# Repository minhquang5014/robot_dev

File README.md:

# robot_dev — Trợ lý giọng nói xiaozhi trên ESP32

Môi trường làm việc cho ESP32 + mic I2S + khuếch đại I2S, chạy firmware
[xiaozhi-esp32](https://github.com/78/xiaozhi-esp32) (MIT) đã tuỳ chỉnh.

## Phần cứng

| Linh kiện | Chi tiết |
|---|---|
| MCU | ESP32-S3-WROOM-1 **N16R8** — 16MB flash, 8MB PSRAM (octal) |
| Mic | INMP441 (I2S) |
| Khuếch đại | MAX98357A (I2S) + loa 4–8Ω |
| Màn hình | OLED SSD1306 128x64 (I2C) |
| Chân robot | 4 servo SG90/MG90S (2 hông + 2 cổ chân) |

Trước 11/10/2026 dự án chạy ESP32-D0WD-V3 4MB **không có PSRAM**. Đổi sang S3 vì
hai lý do: con cũ chết chip USB-serial (cắm 5 lần không lên cổng COM nào), và
PSRAM là điều kiện bắt buộc để chạy wake word trên chip. Board cũ vẫn còn trong
repo ở `main/boards/bread-compact-esp32/`.

### Sơ đồ đấu nối

```
INMP441         ESP32-S3        MAX98357A       ESP32-S3
  VDD    ->      3V3              VIN     ->      5V
  GND    ->      GND              GND     ->      GND
  L/R    ->      GND              DIN     ->      GPIO7
  WS     ->      GPIO4            BCLK    ->      GPIO15
  SCK    ->      GPIO5            LRC     ->      GPIO16
  SD     ->      GPIO6            GAIN    ->      GND (12dB)
                                  SD      ->      để trống
OLED SSD1306    ESP32-S3          +/-     ->      loa 4-8Ω
  VCC    ->      3V3
  GND    ->      GND          Nút BOOT (GPIO0, có sẵn) = bắt đầu/dừng hội thoại
  SDA    ->      GPIO41       GPIO38 = giả lập câu đánh thức
  SCL    ->      GPIO42       GPIO47 = bộ đàm, giữ để nói

Hông trái	GPIO13
Hông phải	GPIO14
Cổ chân trái	GPIO21
Cổ chân phải	GPIO12
```

Tất cả GND chung.

Bản vẽ minh hoạ: [ESP32-S3 Robot Wiring Diagram.png](ESP32-S3%20Robot%20Wiring%20Diagram.png).
Đường dây từ linh kiện tới chân S3 trong ảnh khớp sơ đồ trên, nhưng **lấy sơ đồ chữ
ở trên làm chuẩn** vì ảnh có lỗi:

- Ô "Lưu ý khi hàn dây" ghi servo dùng 3.3V — **sai**, servo dùng 5V nguồn riêng (xem dưới).
- Bảng "Tóm tắt kết nối" lỗi chữ: mic `WS → GPIO45` (đúng là **GPIO4**), `GPIO0 → 3V3`;
  amp `DIN → 5V7`, `LRC → GPIO` thiếu số (đúng: DIN GPIO7, LRC GPIO16).
- Ảnh mic là module electret, không phải INMP441. Servo chỉ vẽ dây tín hiệu, thiếu dây nguồn.
- Nút GPIO38 / GPIO47 chỉ vẽ một dây — chân còn lại của nút nối **GND**.

**Servo phải có nguồn 5V riêng**, chỉ chung mát với board. Lấy từ chân 5V của
DevKitC-1 thì lúc servo giật sẽ kéo sụt cả đường nguồn của S3. Và `MAX98357A VIN`
nối thẳng VBUS không qua ổn áp nào — nên cắm USB qua hub hay cáp kém là tiếng loa
nhỏ hẳn đi. Hàn tụ ~1000 µF sát chân VIN của amp.

**Chân không dùng được trên S3**, khác hẳn ESP32 cũ nên đừng chép sơ đồ cũ sang:

| Chân | Lý do |
|---|---|
| GPIO22–25 | không tồn tại trên S3 (nhảy từ 21 sang 26) |
| GPIO26–32 | SPI flash |
| GPIO33–37 | PSRAM octal của bản R8 |
| GPIO19, 20 | USB D−/D+ |
| GPIO0, 3, 45, 46 | strapping |
| GPIO43, 44 | UART0 (console) |

GPIO12 là chân strapping trên **ESP32 cũ** nhưng **không phải** trên S3, nên ở đây
dùng được cho servo.

### Nguồn pin

| Linh kiện | Chi tiết |
|---|---|
| Pin | LiPo 1 cell **3,7V 3000 mAh**, có mạch bảo vệ (PCM) — mảnh mạch nhỏ dưới băng dính vàng ở đầu pin |
| Sạc + tăng áp | Module Type-C **FM5324GA** (25 x 20 mm): sạc pin qua Type-C, tăng 3,7V lên 5V |
| Công tắc | **Từ 3A trở lên** (ví dụ bập bênh KCD1). Gạt mini SS12D00 / MSK12C02 chỉ 0,3-0,5A — nóng, sụt áp |

```
Pin (+) đỏ ──[CÔNG TẮC ≥3A]── B+ ┐
Pin (−) đen ──────────────────── B− ┤  FM5324GA   5V  ──┬─► ESP32-S3 chân 5V
                                    │             GND ──┼─► GND chung (mọi thứ)
             nút nhấn nhả ── K ─────┘  [Type-C] = sạc   ├─► MAX98357A VIN  (+ tụ 1000 µF)
             (chân kia xuống GND)                       └─► 4 servo dây đỏ (+ tụ 1000 µF)
```

**Chưa chắc chân nào là B+ / B−.** Nhìn ảnh module thì hai miếng hàn cạnh TRÁI (ký hiệu
"□" và "+") là pin, cạnh DƯỚI ("+" và "5V") là ngõ ra — nhưng phải đo trước khi hàn,
ngược cực pin là cháy: cắm Type-C (chưa nối pin), miếng ra ~4,2V là B+, miếng ra ~5V là
ngõ ra; B− thông mạch với GND của ngõ ra.

**Công tắc đặt trên dây đỏ của pin** chứ không phải ở ngõ ra 5V: khi bật tăng áp, module
ăn điện liên tục, ngắt ở ngõ ra thì robot tắt nhưng pin vẫn bị rút. Cái giá: **tắt công
tắc thì không sạc được** — nhớ bật lên khi cắm sạc.

#### Chân K (bật / tắt ngõ ra 5V) — đo ngày 16/10/2026

| Thử | Kết quả |
|---|---|
| Cắm pin, chưa làm gì | Ngõ ra ~3,8V = điện áp pin lọt qua cuộn cảm + diode, **tăng áp chưa chạy** |
| Chạm K xuống GND một cái | Lên **5V** |
| **Hàn cứng K xuống GND** | Giữ 5V được vài phút rồi **tụt xuống 1,6V** — chip hiểu K bị giữ mãi là "nhấn giữ = tắt", tụ ngõ ra xả dần qua đồng hồ đo |

→ **Không hàn cứng K xuống GND.** Dùng K làm nút nguồn (nút nhấn nhả, giống sạc dự phòng):
nhấn một cái để bật. Lúc thử trên chỉ có đồng hồ đo làm tải (gần như 0 mA) — có robot
làm tải (ESP32-S3 ~100 mA trở lên) thì nhiều khả năng mạch không tự tắt. **CHƯA kiểm
chứng:** cắm robot, nhấn K, để chạy 15 phút xem có tự tắt không.

#### Nếu có robot làm tải mà vẫn tự tắt — ESP32 giữ cho mạch thức (CHƯA làm)

Đừng để ESP32 *chờ thấy điện yếu rồi mới* kéo K: ESP32 lấy điện từ chính module này, lúc
tăng áp tắt thì ngõ ra tụt về ≤3,8V, ổn áp 3,3V trên board không đủ đầu vào nên chip sụt áp
và reset trước khi kịp phản ứng. Thay vào đó **nhấn K ngắn theo nhịp, mỗi ~15-20 giây**, để
mạch không bao giờ tự tắt.

Phải thử trước: chạm K xuống GND **thật nhanh (dưới nửa giây) trong lúc đang có 5V** — nếu
5V vẫn giữ thì cách này dùng được; nếu chip hiểu là bật/tắt thì không dùng được.

**Nối THẲNG, không cần transistor.** Chân K lúc nghỉ đo được **0,8V** (17/10/2026) — thấp hơn
3,3V nên nối thẳng vào GPIO không hại gì ESP32:

```
ESP32-S3 GPIO2 ─────── chân K của FM5324GA
```

- Đặt GPIO2 ở chế độ **open-drain**: chỉ có hai trạng thái — kéo xuống GND hoặc thả nổi,
  không bao giờ ra 3,3V. Kéo **xuống 0** ~200 ms rồi thả = một lần "nhấn nút".
- **Đừng** cho GPIO2 ra mức cao: đẩy 3,3V vào K (bình thường 0,8V) là cãi nhau với mạch
  trong chip sạc.
- Lúc ESP32 khởi động GPIO2 mặc định thả nổi nên không bị "nhấn nhầm".
- GPIO2 đang trống trên board S3 (soát với `bread-compact-s3-otto/config.h`).

**Dây K là BẮT BUỘC** — đo ngày 26/10/2026 trên ESP32 WROOM chạy pin, sketch
`test/fm_keepalive` (tự ghi log vào flash):

| Thử | Kết quả |
|---|---|
| ESP32 nhấn K mỗi 15 s (200 ms) | giữ 5V **33,2 phút liền**, 132 lần nhấn, 4,93-5,08V (TB 5,04V), không mất điện lần nào |
| Không nhấn K, ESP32 làm tải (WiFi quét định kỳ, ~100 mA) | mạch **tự tắt**, ngõ ra tụt ~1,5V, ESP32 tắt theo |

→ Nhấn ngắn khi đang bật **không** làm tắt (chip không hiểu là bật/tắt), và có tải vẫn tự tắt —
nên firmware robot phải nhấn K theo nhịp. Board ESP32 cũ (WROOM) dùng GPIO18 vì không ra chân
TX2/RX2; trên board cũ GPIO18 trùng `LAMP_GPIO`, lắp vào robot thì phải dời một trong hai.

**Cắm USB lúc đang chạy pin làm board reset liên tục** (log đầy `POWERON_RESET`) — hai nguồn 5V
đè nhau. Rút pin trước khi cắm USB.

**Đo điện áp pin — tuỳ chọn, có thể bỏ.** Chỉ để báo pin yếu lên OLED; không có thì robot vẫn
chạy, hết pin thì tắt phụt (mạch bảo vệ của pin ngắt ~3,0V, vẫn an toàn). 4 đèn LED trên
module báo mức pin thay được. Nếu muốn làm:

```
5V ──[10 kΩ]──┬──[10 kΩ]── GND
              └── ESP32-S3 GPIO1 (ADC)
```

Chân ADC của ESP32 chỉ đọc tới ~3V, nối thẳng 5V là hỏng. Hai điện trở bằng nhau chia đôi:
5V đọc ra 2,5V, trong code nhân 2. Đọc ~1,9V (tức 3,8V) = tăng áp đã tắt. Rút ~0,25 mA
liên tục; thêm tụ 100 nF từ điểm giữa xuống GND cho số đọc ổn định.

#### Đèn LED khi sạc

Cắm sạc thấy sáng 3/4 đèn dù pin đang ~3,0V là bình thường: lúc có dòng sạc, điện áp ở cực
pin bị đẩy cao hơn mức thật nên đèn báo dư. Muốn biết thật thì rút sạc, để nghỉ 10-15 phút
rồi đo ở hai dây pin (đầy ~4,1-4,2V).

Sạc bằng cục sạc MacBook (USB-C PD) an toàn: không xin thì PD chỉ cấp 5V. Nếu cáp C-to-C
cắm vào không sạc là module thiếu điện trở 5,1 kΩ ở chân CC — dùng cáp USB-A sang C với cục
sạc thường.

#### Pin 3000 mAh có đủ dòng không

Robot kéo tới ~2A ở 5V khi 4 servo cùng giật. Tăng áp lên 5V nên phía pin chịu dòng gấp
~1,6 lần: **pin phải xả ~3,2A**. Pin 3000 mAh dù chỉ xả 1C cũng đã ~3A, nên nhiều khả năng
đủ — nhưng **mạch bảo vệ (PCM) có ngưỡng ngắt quá dòng riêng**, có loại ngắt ở ~3A. Chưa
biết chỉ số xả (C) và ngưỡng PCM của pin này. Thử: cho robot nhảy cả bài trong lúc đang nói;
tắt hoặc reset giữa chừng là PCM đang ngắt.

Ước tính thời gian chạy (chưa đo): 3000 mAh x 3,7V ≈ 11 Wh, qua tăng áp còn ~9 Wh ở 5V →
đứng nghe (~150 mA) **khoảng 10-12 giờ**, nói và đi nhiều **khoảng 3 giờ**.

**Cắm USB nạp code khi đang chạy pin:** hai nguồn 5V có thể đè nhau. Tắt công tắc pin
trước khi cắm USB, hoặc nạp qua WiFi (OTA).

## Tuỳ chỉnh so với xiaozhi gốc

1. **Kết nối được WiFi ẩn** — `xiaozhi-esp32/components/esp-wifi-connect/wifi_station.cc`

   Bản gốc quét WiFi rồi so khớp theo tên. Mạng ẩn không phát tên trong beacon nên
   không bao giờ khớp, thiết bị kẹt ở `No AP found` vĩnh viễn. Bản vá thêm một
   nhánh dự phòng: khi quét không ra, thử kết nối thẳng từng mạng đã lưu —
   `esp_wifi_connect()` gửi probe request có đích danh, và mạng ẩn **có** trả lời.

   Đặt trong `components/` (không sửa `managed_components/`) để không bị ghi đè
   mỗi lần trình quản lý tải lại dependency.

2. **Giao diện tiếng Việt** — `CONFIG_LANGUAGE_VI_VN=y` trong `sdkconfig`.
   Cả chữ trên màn lẫn giọng đọc. Font mặc định đã phủ đủ 39 ký tự có dấu được dùng.

3. **OLED 128x64** — `CONFIG_OLED_SSD1306_128X64=y` (mặc định của board là 128x32).

4. **Đánh thức bằng tên "Sophia"** — `CONFIG_SR_WN_WN9_SOPHIA_TTS=y`.

   Thay cho `CONFIG_ALWAYS_LISTENING` cũ (rảnh ~5 giây là tự mở hội thoại). Chế độ
   cũ làm robot trả lời **mọi** câu nó nghe được và gửi tiếng lên server 100% thời
   gian; giờ nằm im cho tới khi nghe đúng tên.

   Vì sao là "Sophia": model WakeNet đóng gói sẵn trong `esp-sr` có 75 cái, lọc bỏ
   tiếng Trung còn 39 — **không có tiếng Việt**. Trong nhóm tên nữ, "Sophia" là cái
   **duy nhất gọi trống được**; mọi tên khác đều buộc kèm "Hey"/"Hi" (Hey Ivy,
   Hi Fairy…). Muốn đúng tên tiếng Việt thì phải đặt model riêng của Espressif.

   Ba thứ phải khớp nhau nếu đổi tên: model trong `sdkconfig`, chuỗi
   `WakeWordInvoke` trong board `.cc`, và `ROBOT_NAME`/`WAKE_PATTERN` trong
   `server/pipeline.py`.

   **Luồng:** nằm chờ ở Idle, không gửi gì lên mạng — mic chỉ chạy vào
   `[VAD(WebRTC)] -> [WakeNet]` trong chip. Nghe thấy tên → giữ lại đoạn tiếng đó
   (`CONFIG_SEND_WAKE_WORD_DATA=y`, thiếu nó thì bản ghi không chứa tên và bộ lọc
   tên phía server loại sạch mọi lượt) → mở kênh, gửi Opus 60 ms → server quyết
   định lượt kết thúc → trả lời → **về lại Idle**.

   Lưu ý có **hai VAD làm hai việc khác nhau**: cái trong chip chỉ để gác WakeNet
   cho đỡ tốn điện; cái trên server mới quyết định người nói đã dứt câu chưa.

   Cái giá: phải gọi tên **mỗi lượt**, không nói tiếp được. Cửa sổ 20 giây hỏi tiếp
   không cần gọi tên (`WAKE_WINDOW_S` trong `xiaozhi_server.py`) vì thế thành vô
   dụng — thiết bị về Idle ngay nên không gửi gì lên trong quãng đó.

   Hai mắt xích đã phải vá để wake word thật sự gác được, vì bật model thôi chưa đủ:
   `application.cc` nhận `tts stop` chỉ về Idle khi chế độ là `ManualStop`, còn
   `AutoStop` thì quay lại Listening; và chế độ `AutoStop` nghĩa là thiết bị chờ
   server báo hết lượt, mà server lại huỷ lượt rỗng trong im lặng — nay gửi cặp
   `tts start`+`stop` rỗng (`ket_thuc_luot`) để báo.

5. **Server tự host** — `CONFIG_OTA_URL` trỏ về `https://xiaozhi-esp32-server.fly.dev/xiaozhi/ota/`
   thay vì `api.tenclass.net`. Không cần đăng ký mã trên xiaozhi.me nữa.

6. **Nâng cấp qua WiFi (OTA)** — chỉ chạy được từ khi sang board 16MB.

   Bảng `partitions/v2/16m.csv` có hai khe `ota_0`/`ota_1`. Board 4MB cũ chỉ có một
   phân vùng `factory`, và hai khe cũng **không nhét vừa** 4MB — nên OTA trên nó là
   bất khả thi, không phải chuyện cấu hình.

   Firmware vốn đã có sẵn code OTA; phần thiếu là server không trả khoá `firmware`.
   Quy trình phát hành xem `server/firmware/.gitkeep`. Server đọc phiên bản và mã
   chip **thẳng từ file `.bin`** nên không có tệp phụ nào để lệch.

   Firmware chỉ hỏi OTA **một lần lúc khởi động** (`application.cc`, `CheckNewVersion`),
   không có hẹn giờ định kỳ — muốn nâng cấp thì bấm reset.

## Cài môi trường (macOS, không cần sudo)

```bash
# ESP-IDF v6.1 — xiaozhi yêu cầu >= 6.0.1, KHÔNG chạy trên 5.x
git clone -b v6.1 --recursive --depth 1 --shallow-submodules \
    https://github.com/espressif/esp-idf.git ~/esp/esp-idf
cd ~/esp/esp-idf && ./install.sh esp32s3

# macOS không kèm cmake/ninja cho ESP-IDF, cài vào venv của nó:
. ~/esp/esp-idf/export.sh && python -m pip install cmake ninja
```

Nếu gặp `CERTIFICATE_VERIFY_FAILED`: bản Python từ python.org thiếu chứng chỉ gốc.
Sửa bằng `python3 -m pip install --user certifi` rồi
`export SSL_CERT_FILE=$(python3 -c "import certifi;print(certifi.where())")`.

Với các sketch Arduino, cần `arduino-cli` + core `esp32:esp32`.

## Build và nạp

```bash
cd xiaozhi-esp32
. ~/esp/esp-idf/export.sh
idf.py set-target esp32s3    # chỉ lần đầu
idf.py build
idf.py -p /dev/cu.usbserial-XXXX flash monitor
```

> **Đường dẫn repo không được có dấu cách.** Với đường dẫn kiểu `~/Documents/2. Py/...`
> bước link hỏng: `ld: cannot find Py/2.Raw/19.: No such file or directory` — thư viện
> prebuilt của `esp_audio_codec` bị cắt đôi ở dấu cách. Clone vào chỗ khác, ví dụ `~/esp/robot_dev`.

Sau khi nạp, thiết bị phát hotspot `Xiaozhi-XXXX`. Nối điện thoại vào, mở
`http://192.168.4.1` để khai báo WiFi (chỉ 2.4GHz). Với server trong `server/`
thì thiết bị tự nói chuyện luôn, không cần đăng ký mã tại xiaozhi.me.

## Script tiện ích (`scripts/`)

Copy vào `~/bin` và thêm vào PATH:

| Lệnh | Việc |
|---|---|
| `xz build \| flash \| mon \| all` | Build/nạp/xem log xiaozhi |
| `esp build \| up \| mon <thư_mục>` | Tương tự cho sketch Arduino |
| `mic-rec [--level] [-o ten.wav]` | Ghi âm từ mic về máy tính, nghe lại kiểm tra |
| `xz-wifi "Tên Mạng"` | Khai báo WiFi cho ESP32 qua hotspot của nó |

Sửa biến `PORT` / `XZ_PORT` / `MIC_PORT` trong script cho khớp cổng máy bạn.

## Sketch kiểm tra phần cứng

- `mic_record/` — đẩy PCM thô qua serial, dùng với `mic-rec` để nghe lại giọng mình
- `xz_audio_test/` — phát bíp 1kHz mỗi 5 giây (test loa) + in mức mic (test mic)

Cả hai đều dùng chân giống xiaozhi nên test xong là biết phần cứng có vấn đề không.

> **Lưu ý khi tự viết code I2S:** phải đặt `.mck_io_num = I2S_PIN_NO_CHANGE`.
> Bỏ trống thì nó mặc định thành GPIO0; kênh I2S thứ hai sẽ báo `mclk config failed`
> và `i2s_set_pin()` **thoát sớm, chưa kịp gán BCLK/LRC/DIN** — loa câm dù phần cứng tốt.

## Máy chủ

### Mặc định: máy chủ chính thức của xiaozhi

Firmware nối ra ngoài theo **hai tầng**:

1. **Kích hoạt và cấp phát** — thiết bị gọi `https://api.tenclass.net/xiaozhi/ota/`,
   địa chỉ viết cứng ở `main/Kconfig.projbuild:5` (sửa qua `CONFIG_OTA_URL`).
   Trang `xiaozhi.me` là nơi bạn đăng nhập để gán thiết bị vào tài khoản; còn
   ESP32 thì nói chuyện với `api.tenclass.net`. Cùng nhà vận hành, khác vai trò.

2. **Hội thoại** — máy chủ ở tầng 1 trả về cấu hình MQTT/WebSocket, firmware lưu
   vào NVS (`main/ota.cc:152-180`). Địa chỉ server hội thoại **không nằm trong code**
   mà do server cấp phát lúc kích hoạt.

> **Về riêng tư:** giọng nói được gửi lên máy chủ của bên vận hành xiaozhi (Trung Quốc)
> để nhận dạng và sinh câu trả lời. ESP32 chỉ thu, nén Opus và truyền đi.
> `api.tenclass.net` cũng là điểm chặn duy nhất — server đó hỏng hoặc chặn IP là
> thiết bị thành cục gạch.

### Tự host

**[`server/`](server/README.md) — server duy nhất của repo**, tự viết, deploy lên Fly.io
bằng `fly deploy` ngay trong thư mục đó. Groq Whisper + `qwen3.8-27b` + xAI TTS, tiếng
gửi xuống 24 kHz đúng tần số loa, có lọc câu ảo giác cho chế độ luôn nghe.
**Điều khiển chân bằng giọng nói** qua MCP: LLM gắn tag động tác ngay sau tag cảm
xúc (`[joyful][dance]`), server gửi `tools/call self.otto.action` xuống firmware
**trước** TTS. Cố ý không dùng function calling của LLM vì thêm một vòng gọi API
và hay vỡ khi stream.

**Điều khiển bằng chữ từ máy tính** — `server/say.py`, khỏi phải nói:

```bash
python say.py "nhảy một điệu đi"   # y như vừa nói: LLM -> cảm xúc + động tác + TTS
python say.py --do dance           # bắn thẳng động tác, KHÔNG qua LLM, không tốn TTS
python say.py --do walk --steps 4
python say.py --liet-ke            # 15 động tác hợp lệ
```

`--do` mới là thứ dùng khi thử dáng đi: phải lặp cùng một lệnh hàng chục lần, mà
mỗi lượt qua LLM là một lần gọi Groq (bản miễn phí chỉ 20 STT/phút).

Hai endpoint này (`/xiaozhi/say`, `/xiaozhi/do`) mở một cửa điều khiển ra Internet
nên **có mật khẩu**: header `Authorization: Bearer`, đặt bằng
`fly secrets set XZ_CTRL_TOKEN=...` chứ không ghi vào `fly.toml` (tệp đó nằm trong
git). Không đặt secret thì hai cửa **đóng** (503) chứ không mở toang. `say.py` tự
đọc mật khẩu từ `server/.env`.

Trước 06/10/2026 repo còn `fly-server/`: bọc [xiaozhi-esp32-server](https://github.com/xinnan-tech/xiaozhi-esp32-server)
(dự án cộng đồng, đủ MCP) kèm bản vá. Đã bỏ vì chậm (đo 06/10: ~15 s tới câu trả lời đầu)
và hay dính mặc định tiếng Trung. Xem lại trong lịch sử git nếu cần.

**Đổi server không cần nạp lại firmware.** Firmware đọc `ota_url` lưu trong NVS trước,
trống mới dùng `CONFIG_OTA_URL` (`main/ota.cc:48-55`). Đặt được qua trang cấu hình WiFi
`http://192.168.4.1`, tab nâng cao.

#### Bộ miễn phí, có tiếng Việt

> **Groq không phải Grok.** Hai công ty khác nhau. **Grok** là LLM của xAI, trả tiền.
> **Groq** là công ty phần cứng suy luận, nổi tiếng vì tốc độ, và free tier rất rộng.
> Nhầm hai cái này là mất tiền oan.

| Tầng | Chọn | Hạn mức miễn phí |
|---|---|---|
| STT | Groq `whisper-large-v3-turbo` | 2.000 req/ngày, 28.800 giây audio/ngày |
| LLM | Groq `qwen/qwen3.8-27b` | ~1.000 req/ngày, **8.000 token/phút** |
| TTS | EdgeTTS, `vi-VN-HoaiMyNeural` / `vi-VN-NamMinhNeural` | Không giới hạn thực tế |

Tổng chi phí **$0/tháng**, không cần thẻ tín dụng. Groq tương thích chuẩn OpenAI nên
cắm thẳng vào khe LLM. Chỗ siết thật là **token/phút** chứ không phải request/ngày:
mỗi lượt ~700 token, tức trần khoảng 11 lượt/phút — robot để bàn thì thoải mái.

> **Groq gỡ model theo thời gian.** Bản trước của README này khuyến nghị
> `llama-3.1-8b-instant`; đến 16/09/2026 model đó đã bị gỡ. Chạy
> `python server/test_voice.py --models` trước khi tin bất kỳ tên model nào ở đây.
> Số đo và so sánh các model: [server/README.md](server/README.md).

**Đừng dùng FunASR cho tiếng Việt** — nó tối ưu cho tiếng Trung. Muốn chạy STT
hoàn toàn cục bộ thì dùng faster-whisper.

Nếu cần suy luận mạnh hơn, **Grok (xAI) cắm được thẳng vào khe LLM** vì API chat của
họ đúng chuẩn OpenAI. Grok cũng có STT/TTS riêng (`https://api.x.ai/v1/tts`,
$4.20 / 1 triệu ký tự ~ 5000 lượt đối đáp) nhưng server dùng danh sách provider cố
định **không có xAI**, nên hai phần đó phải tự viết adapter.

**LiveKit không hợp ở đây.** Nó là hạ tầng WebRTC + điều phối agent, bản thân không
phải nhà cung cấp STT. ESP32 nói giao thức riêng của xiaozhi chứ không phải WebRTC,
nên ghép vào là phải viết cầu nối hai giao thức mà chẳng được gì thêm.

#### Đặt server ở đâu

ESP32 chỉ mở kết nối **đi ra** (y như nó đang gọi `api.tenclass.net`), nên:

- **VPS có IP công cộng — dễ nhất.** Mạng nhà hay mạng ESP32 đang bám không cần cấu
  hình gì. Oracle Cloud Always Free cho 4 nhân ARM / 24GB vĩnh viễn là quá đủ, nhược
  điểm là nhiều khu vực hay hết chỗ ARM, phải thử lại nhiều lần.
  **Trên VPS thì vẫn phải mở cổng server**, và với Oracle là mở ở **cả hai chỗ**:
  security list của VCN, và iptables bên trong máy (image Ubuntu của Oracle chặn sẵn).
  Thiếu một trong hai là ESP32 báo không kết nối được.
- **Máy ở nhà — vướng mạng.** Chỉ chạy khi ESP32 **cùng mạng LAN**, hoặc bạn mở được
  port ra ngoài. Nếu ESP32 đang bám hotspot điện thoại hay máy in thì gần như chắc
  chắn không mở port được. Đây là lựa chọn khó hơn, không phải dễ hơn.
- **Máy công ty — đừng.** Mở cổng hay dựng tunnel (cloudflared, ngrok…) trên máy do
  công ty quản lý là đi vòng tường lửa của họ, IT theo dõi đúng loại việc này. Dùng
  máy công ty để sửa code, nạp firmware qua USB, đọc log là đủ; server đặt trên VPS.

#### Với robot kiểu thú cưng thì tối ưu cái gì

Thứ quyết định "dễ thương" không nằm ở kích cỡ model:

- **Độ trễ ăn đứt độ thông minh.** Trả lời ngốc nghếch sau 0,8 giây dễ thương hơn hẳn
  câu sâu sắc sau 4 giây — im lặng 4 giây trông như treo máy. Đó là lý do chọn Groq.
- **Câu trả lời phải ngắn.** Thú cưng không thuyết trình. Ép system prompt giới hạn
  1–2 câu: vừa nhanh, vừa đáng yêu, vừa đỡ tốn TTS.
- **Tính cách nằm ở system prompt.** Model vừa phải với prompt nhân vật viết kỹ sống
  động hơn model lớn trả lời trung tính. Đây là chỗ đáng bỏ công nhất mà lại miễn phí.
- **Model nhỏ nhất chưa chắc nhanh nhất.** Trên Groq tốc độ phụ thuộc phần cứng họ phục
  vụ, không phụ thuộc kích cỡ. Đo 17/09/2026: `allam-2-7b` (nhỏ nhất) trung vị 419 ms
  và nói tiếng Việt hỏng, còn `qwen3.8-27b` trung vị 362 ms và nói tốt.
- **Giọng đọc quan trọng ngang nội dung.** EdgeTTS chỉnh được tốc độ và cao độ; nói
  nhanh hơn một chút thường nghe trẻ trung, hợp kiểu robot cute.

### Chưa kiểm chứng

- Server tự viết trong `server/` chưa được ESP32 thật gọi vào — mới qua thiết bị giả lập.
- Chưa tự đăng ký Oracle Cloud Always Free nên không dám hứa lấy được máy ARM ngay.
- Hạn mức Groq ở bảng trên lấy từ header trả về khi chạy thật, nhưng chưa chạy đủ
  lâu để chạm trần ngày.
- Đổi server **không** cứu được chuyện thiếu wake word — đó là giới hạn phần cứng.

## Hạn chế đã biết

Không có PSRAM nên **không dùng được wake word** (`USE_ESP_WAKE_WORD` cần
`IDF_TARGET_ESP32 && SPIRAM`) và **không có AEC** (`USE_AUDIO_PROCESSOR` cần S3/P4 +
PSRAM). Chế độ luôn nghe (tuỳ chỉnh 4) thay cho wake word nhưng trả lời mọi câu nghe được,
và robot không nghe trong lúc đang nói. Muốn gọi tên mới tỉnh hoặc ngắt lời bằng giọng thì
cần module có PSRAM, phổ biến nhất là ESP32-S3.

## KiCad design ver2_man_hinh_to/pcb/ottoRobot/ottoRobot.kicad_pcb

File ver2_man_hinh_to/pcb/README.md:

# Mạch chính Otto ver2

Bo mạch custom cho robot ver2: ESP32-S3-WROOM-1 N16R8 hàn thẳng, màn ST7789
240×240 qua SPI, Otto 2 chân, loa khoang 8Ω 2W, mic INMP441.

Mở bằng KiCad 10. File dự án: `otto-ver2.kicad_pro`.

## Mạch to bao nhiêu thì còn nhét vừa thân

Đo trực tiếp trên `../3D-print/vo-than-noi-luoi-loa.stl` bằng cách quét tia
theo trục z ở từng độ cao, lấy bóng ngoài trừ đi nhựa, rồi trừ tiếp mọi vật
thể đã chiếm chỗ. Tiêu chí: hình chữ nhật phải còn **rỗng liên tục 11mm**
tính từ đáy mạch (1,6mm bo + ~10mm linh kiện cao nhất).

| Vị trí | Cao độ đáy | Lớn nhất | Diện tích |
|---|---|---|---|
| Lọt giữa hai servo | z = 8…24 | 37 × 38 mm | 1.406 mm² |
| **Nằm trên servo như nắp** | **z = 31** | **65 × 46 mm** | **2.990 mm²** |

Chọn phương án nằm trên. Ở z=31 nó cao hơn mọi thứ bên dưới: servo tới 25,
IP5306 tới 30, vách pin tới 31. Thân cao 42 nên còn đúng 11mm.

**Biên mạch lấy 64 × 45mm**, chừa 0,5mm hở mỗi cạnh so với 65 × 46 đo được.

### Các vật thể đã trừ khi đo

| Vật thể | x | y | z |
|---|---|---|---|
| Màn hình (mô-đun 40×33×5 áp sau cửa sổ) | −20…20 | −32,5…−27,5 | 5…38 |
| Loa (trên lưới thoát âm) | −12,5…12,5 | −16…−0,5 | 2…7 |
| Servo trái | −31…−19 | −18…7 | 2…25 |
| Servo phải | 19…31 | −18…7 | 2…25 |
| IP5306 | 8,5…33,5 | 11…15 | 10…30 |
| Vách pin | −13,5…34,5 | 15,5…18,5 | 2…31 |
| Pin LiPo 104058 dựng đứng | −9,5…30,5 | 18,5…28,5 | 2…60 |

Cửa sổ mặt trước đo được **30,5 × 30,5mm** ở `x −15…15, z 6,5…36,5` — vùng
hiển thị 27,7 × 27,7 của màn 1.54" lọt thoải mái.

Chiều cao servo `z 2…25` là **ước lượng theo thân SG90 (22,5mm)**, không đo
được từ file thân vì servo không nằm trong đó. Rãnh sàn đo được 12 × 25mm,
khớp đúng tiết diện thân SG90 (12,6 × 22,8), và mã rig trong `viewer.html`
ghi "cần servo cắm từ sàn xuống" nên thân servo nằm trên sàn. Nếu lắp thật
thấy khác thì phải đo lại cao độ z=31.

## Hệ toạ độ

```
PCB_x = robot_x + 150
PCB_y = 100 − robot_y
```

Mạch nằm ở `z = 31` trong thân. Biên mạch phủ `robot x −32…32, y −27…18`.

Bốn lỗ vít M2 (Ø2,2) ở `robot (±28, −23)` và `(±28, 14)`. **Thân in chưa có
trụ bắt vít** — phải thêm vào `vo-than-noi-luoi-loa.stl` trước khi in.

## Sơ đồ chân

ESP32-S3-WROOM-1 N16R8 dùng được: 0–18, 21, 38–42, 45–48.
Tránh: 19/20 là USB D−/D+, 22–25 không tồn tại, 26–32 nuôi flash,
**33–37 nuôi PSRAM octal** của bản R8, 43/44 là UART0.

| Khối | Chân |
|---|---|
| Màn ST7789 SPI | CLK 18 · MOSI 17 · DC 8 · RST 9 · BLK 10 |
| Mic INMP441 I2S | WS 4 · SCK 5 · DIN 6 |
| Loa MAX98357A I2S | DOUT 7 · BCLK 15 · LRCK 16 |
| Servo | chân trái 13 · chân phải 14 · cổ trái 21 · cổ phải 12 |
| Nút | BOOT 0 · TOUCH 47 · ASR 38 |

Còn trống: **1, 2, 3, 11, 39, 40, 41, 42, 45, 46, 48**. Dự định dùng:

- **Đo điện áp pin** — bắt buộc ADC1 (GPIO 1–10) vì ADC2 đụng WiFi; trong
  nhóm đó chỉ còn 1, 2, 3 trống. Ver1 không có nên không biết pin còn bao nhiêu.
- **Chân KEY giữ mạch sạc không tự tắt** — ver1 dùng GPIO2, giữ nguyên cho đồng bộ.
- **LED trạng thái** — GPIO48, đúng chân ver1 dùng.
- **I2C dự phòng** — 41/42, cặp ver1 dùng cho OLED.

Số chân khớp với `../xiaozhi-esp32/main/boards/s3-otto-lcd/config.h`. Đổi ở
một nơi thì phải đổi cả hai.

## Lưu ý thiết kế

- **Vùng anten.** Chỗ anten WROOM-1 phải không có đồng ở mọi lớp, và nên
  quay về phía trước (`y −27`). Cục pin LiPo ở `y 18,5…28,5` có vỏ nhôm,
  chắn 2,4GHz.
- **Dòng servo.** 4 con SG90 lúc khởi động kéo đỉnh ~2,5A. Đường nguồn servo
  tách riêng khỏi nguồn 3,3V của MCU, dùng net class `Power` (đường 1,0mm),
  và cần tụ lớn ngay tại cổng servo.
- **Cỡ linh kiện 0805/0603, chân rộng** — hàn tay được mà đặt máy hàn cũng được.

## Chưa làm

- Phần sạc/nguồn pin: chờ bản vẽ tham khảo.
- Schematic mới chỉ là khung rỗng.
- Thân in chưa có trụ bắt vít cho mạch.

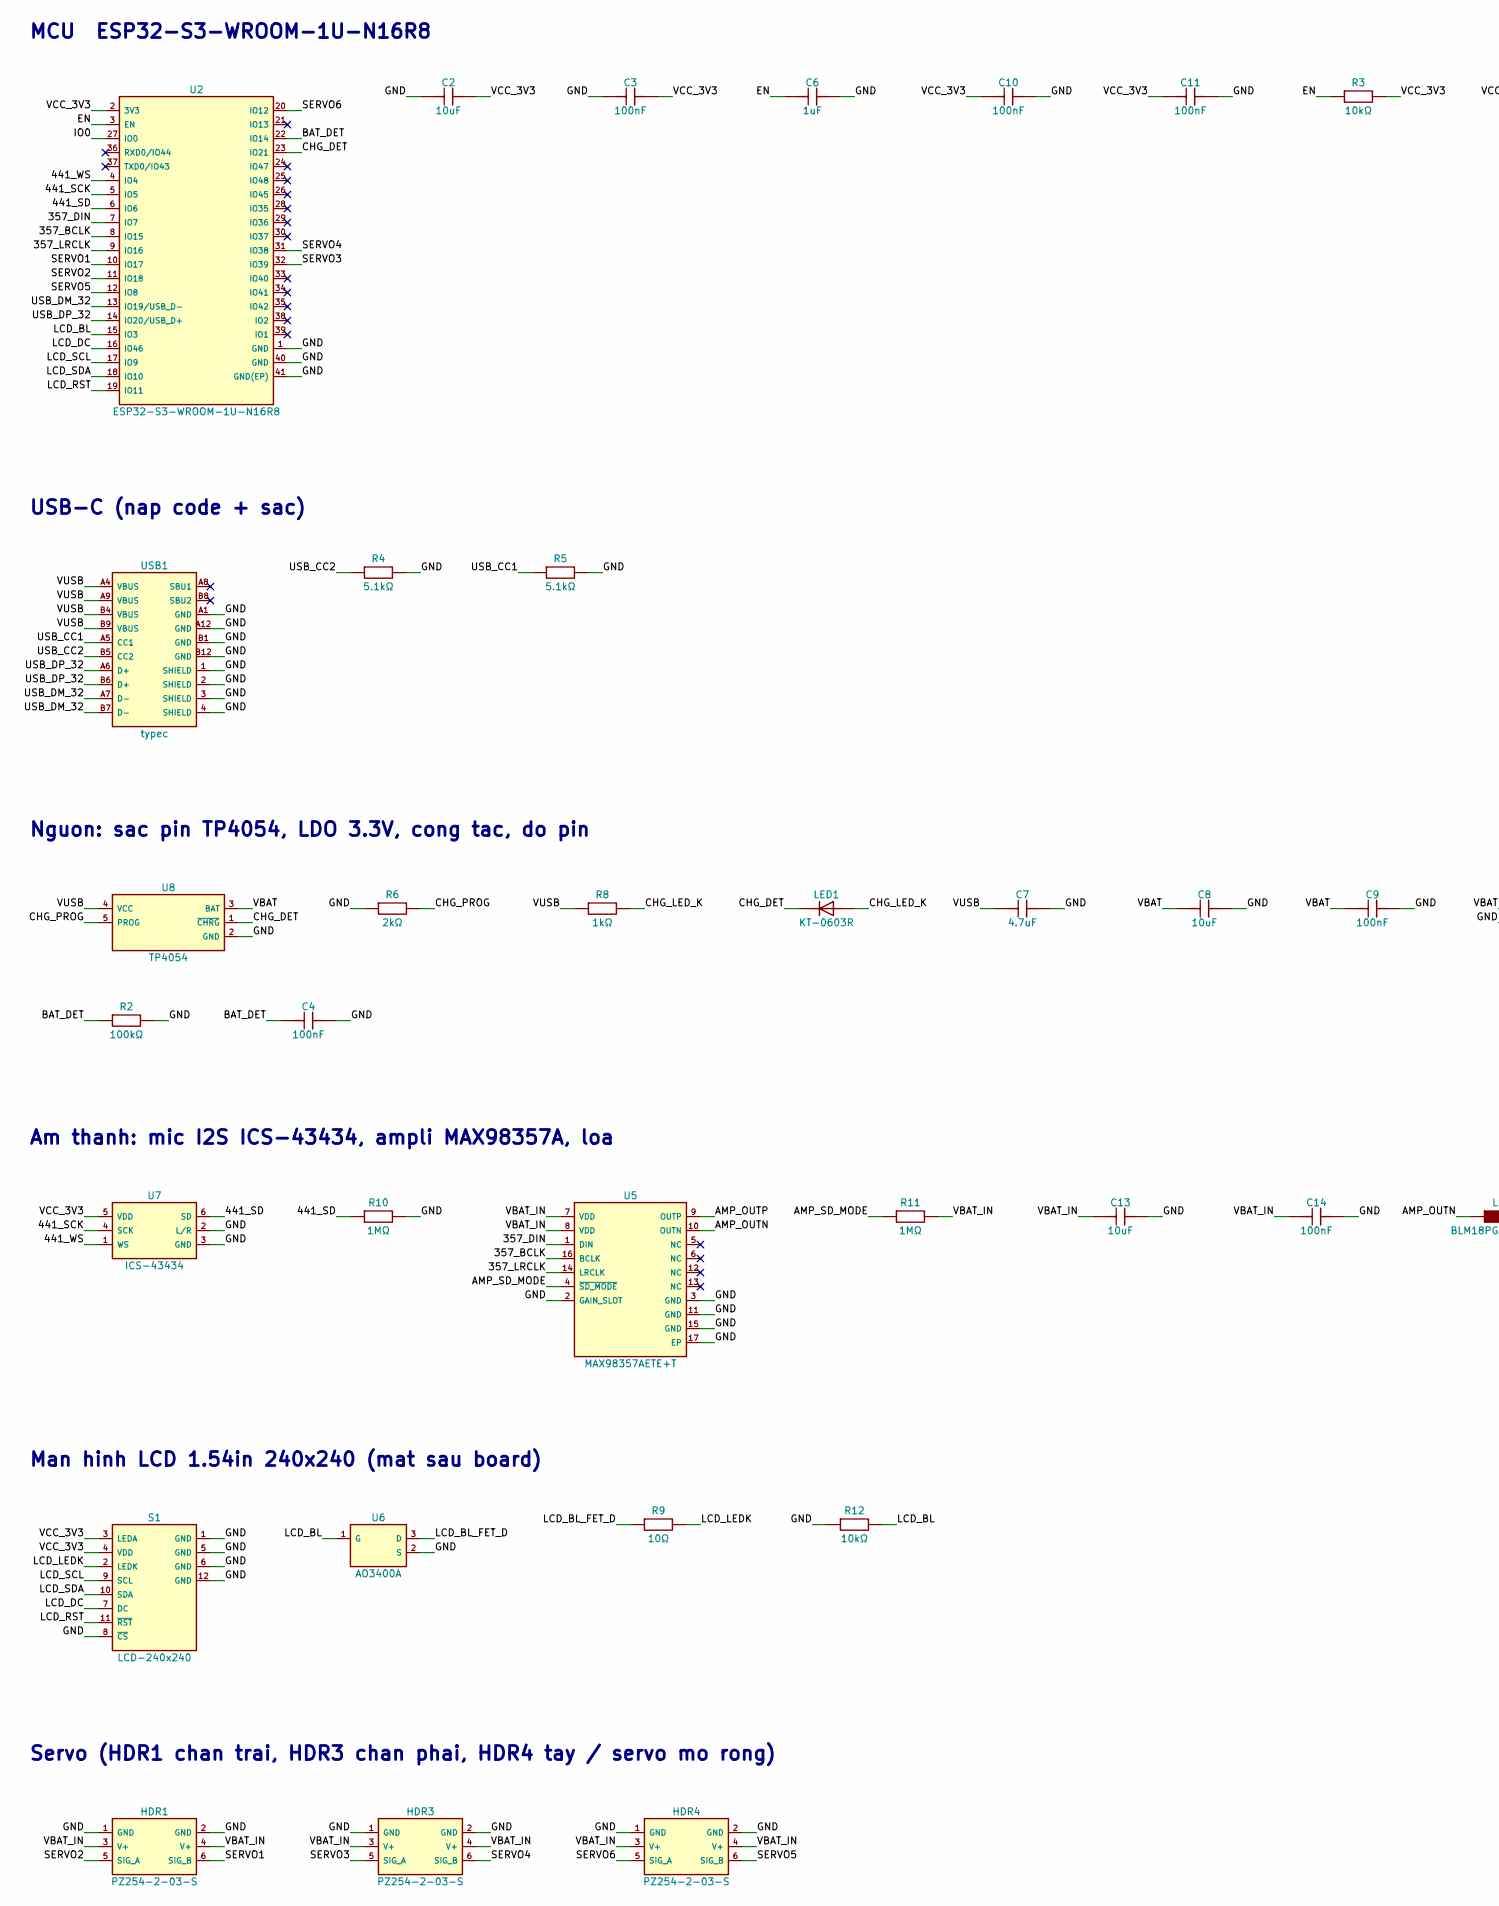
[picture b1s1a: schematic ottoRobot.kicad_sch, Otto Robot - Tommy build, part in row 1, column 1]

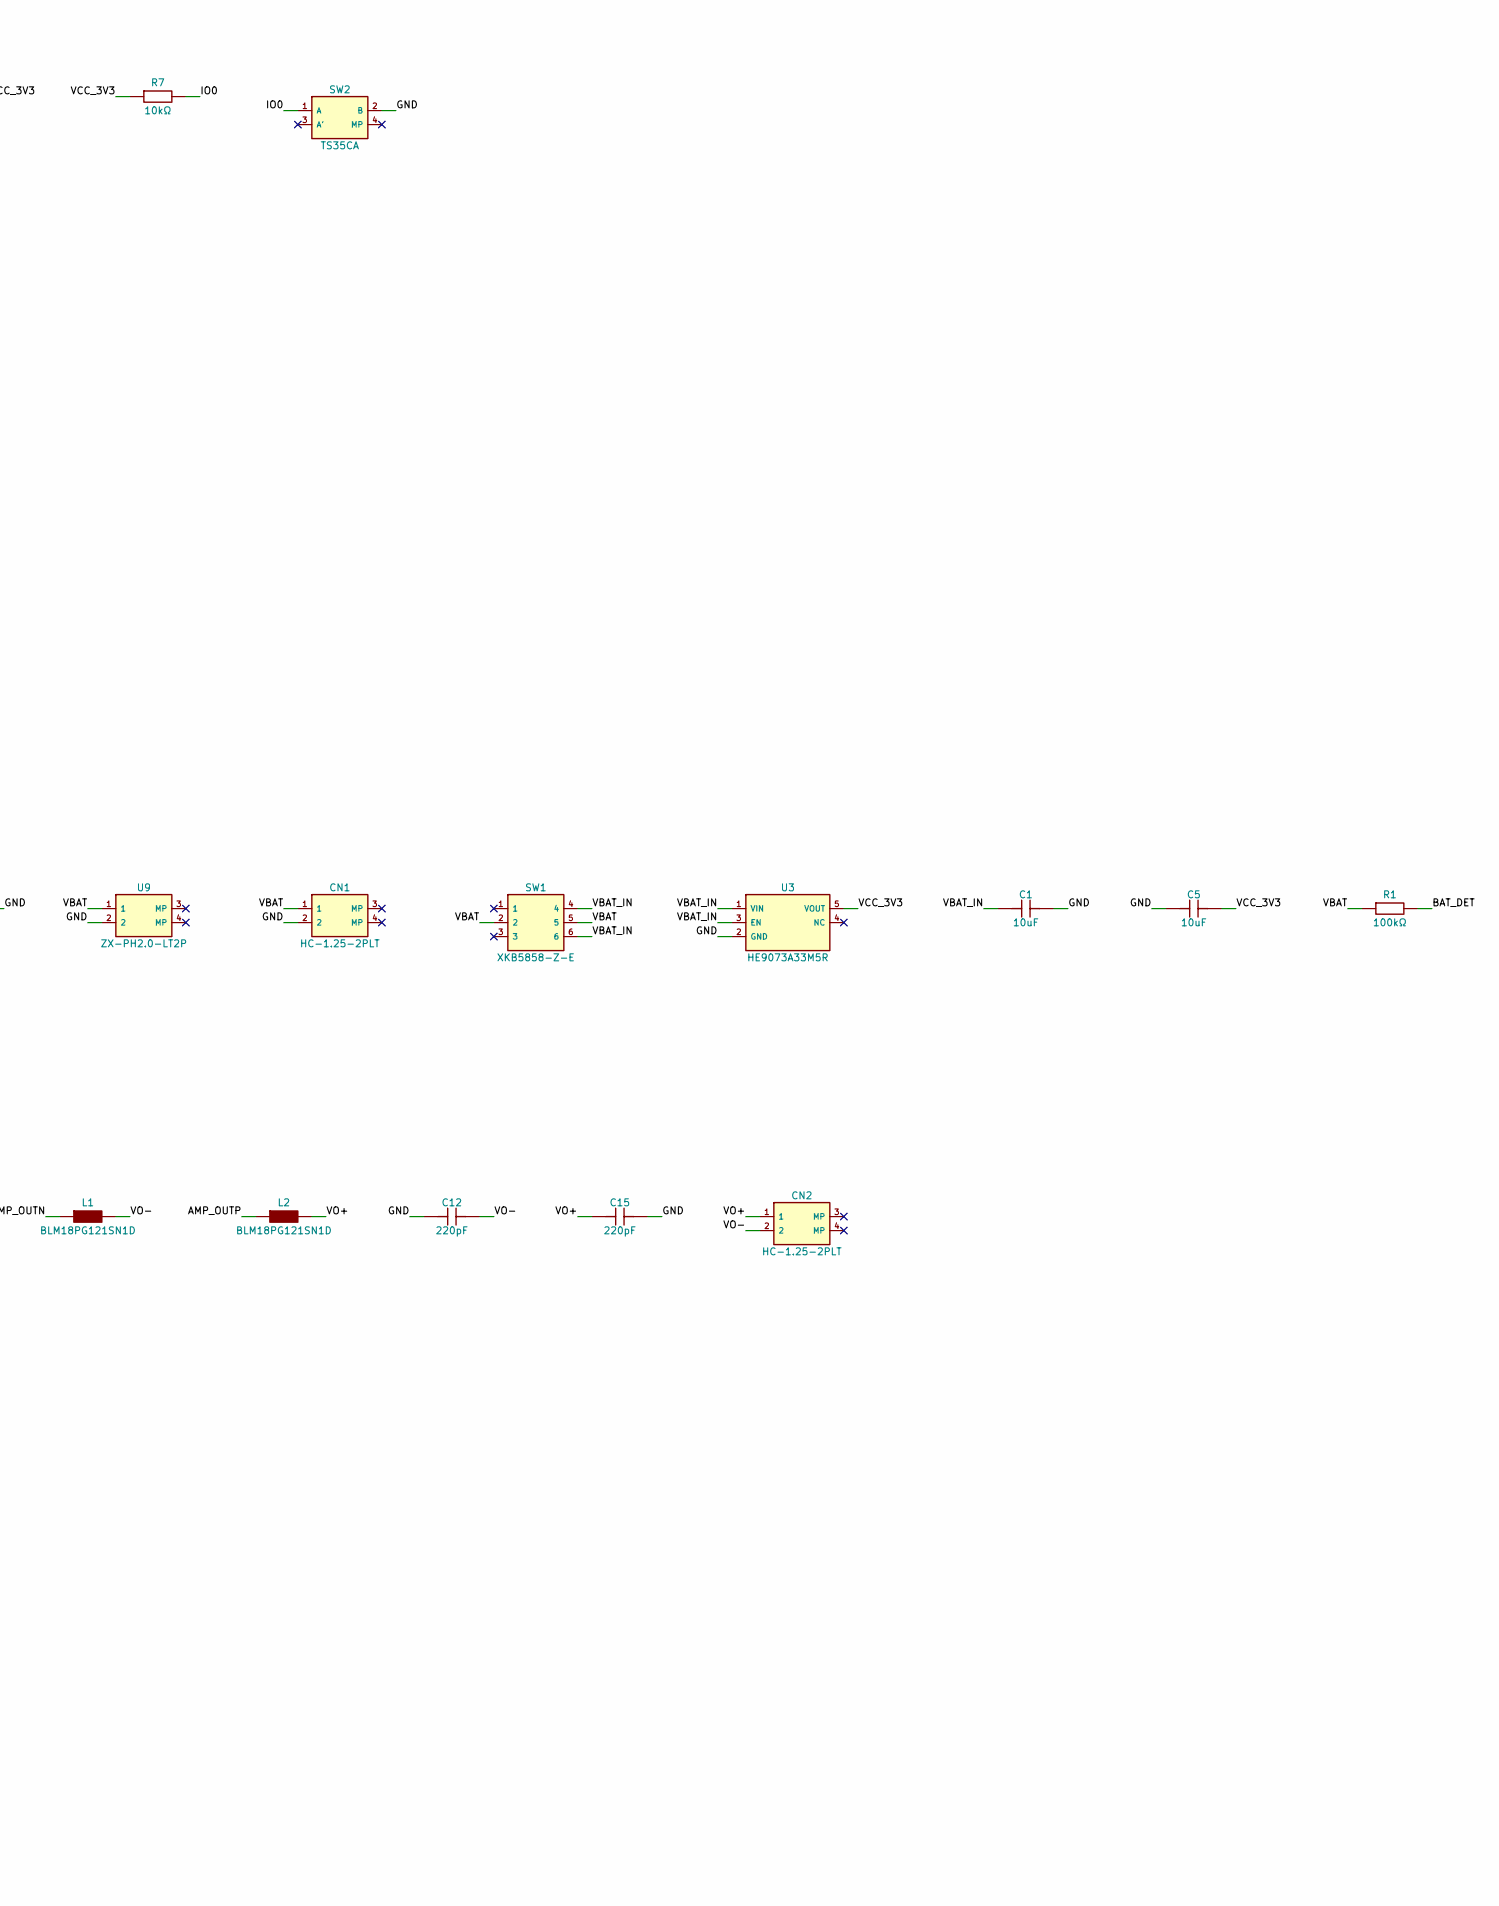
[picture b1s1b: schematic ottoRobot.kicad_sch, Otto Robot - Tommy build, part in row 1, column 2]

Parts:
C1, C2, C5, C8, C13: 10uF; C0603; MPN CL10A106KP8NNNC; LCSC C19702
C3, C4, C9, C10, C11, C14: 100nF; C0603; MPN CC0603KRX7R9BB104; LCSC C14663
C6: 1uF; C0603; MPN CL10A105KB8NNNC; LCSC C15849
C7: 4.7uF; C0603; MPN CL10A475KO8NNNC; LCSC C19666
C12, C15: 220pF; C0603; MPN CL10B221KB8NNNC; LCSC C1603
CN1, CN2: HC-1.25-2PLT; CONN-SMD_HC-1.25-2PLT; MPN HC-1.25-2PLT; LCSC C2845388
HDR1, HDR3, HDR4: PZ254-2-03-S; HDR-SMD_6P-P2.54-V-M-R2-C3-LS7.5-2; MPN PZ254-2-03-S; LCSC C3294461
L1, L2: BLM18PG121SN1D; L0603; MPN BLM18PG121SN1D; LCSC C14709
LED1: KT-0603R; LED0603-RD; MPN KT-0603R; LCSC C2286
R1, R2: 100kΩ; R0603; MPN 0603WAF1003T5E; LCSC C25803
R3, R7, R12: 10kΩ; R0603; MPN 0603WAF1002T5E; LCSC C25804
R4, R5: 5.1kΩ; R0603; MPN 0603WAF5101T5E; LCSC C23186
R6: 2kΩ; R0603; MPN 0603WAF2001T5E; LCSC C22975
R8: 1kΩ; R0603; MPN 0603WAF1001T5E; LCSC C21190
R9: 10Ω; R0603; MPN 0603WAF100JT5E; LCSC C22859
R10, R11: 1MΩ; R0603; MPN 0603WAF1004T5E; LCSC C22935
S1: LCD-240x240; LCD-240x240-FlUSH-154
SW1: XKB5858-Z-E; SW-TH_XKB5858-Z-E; MPN XKB5858-Z-E; LCSC C780038
SW2: TS35CA; KEY-SMD_TS35CA; MPN TS35CA; LCSC C412366
U2: ESP32-S3-WROOM-1U-N16R8; WIRELM-SMD_ESP32-S3-WROOM-1U; MPN ESP32-S3-WROOM-1U-N16R8; LCSC C3013946
U3: HE9073A33M5R; SOT-23-5_L3.0-W1.7-P0.95-LS2.8-BL; MPN HE9073A33M5R; LCSC C723789
U5: MAX98357AETE+T; TQFN-16_L3.0-W3.0-P0.50-BL-EP1.5; MPN MAX98357AETE+T; LCSC C910544
U6: AO3400A; SOT-23-3_L2.9-W1.3-P1.90-LS2.4-BR; MPN AO3400A; LCSC C347475
U7: ICS-43434; MIC-SMD_6P-L3.5-W2.7-P0.90-BL; MPN ICS-43434; LCSC C5656610
U8: TP4054; TSOT-23-5_L2.9-W1.6-P0.95-LS2.8-BR; MPN TP4054; LCSC C668215
U9: ZX-PH2.0-LT2P; CONN-SMD_2P-P2.00_ZX-PH2.0-LT2P; MPN ZX-PH2.0-LT2P; LCSC C7429698
USB1: typec; USB-C-SMD_KH-TYPE-C-16P; MPN typec; LCSC C9900016956

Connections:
357_BCLK: U2.8 (IO15), U5.16 (BCLK)
357_DIN: U2.7 (IO7), U5.1 (DIN)
357_LRCLK: U2.9 (IO16), U5.14 (LRCLK)
441_SCK: U2.5 (IO5), U7.4 (SCK)
441_SD: R10.1, U2.6 (IO6), U7.6 (SD)
441_WS: U2.4 (IO4), U7.1 (WS)
AMP_OUTN: L1.1, U5.10 (OUTN)
AMP_OUTP: L2.1, U5.9 (OUTP)
AMP_SD_MODE: R11.1, U5.4 (~SD_MODE)
BAT_DET: C4.1, R1.2, R2.1, U2.22 (IO14)
CHG_DET: LED1.1 (K), U2.23 (IO21), U8.1 (~CHRG)
CHG_LED_K: LED1.2 (A), R8.2
CHG_PROG: R6.2, U8.5 (PROG)
EN: C6.1, R3.1, U2.3 (EN)
GND: C1.2, C2.1, C3.1, C4.2, C5.1, C6.2, C7.2, C8.2, C9.2, C10.2, C11.2, C12.1, C13.2, C14.2, C15.2, CN1.2, HDR1.1 (GND), HDR1.2 (GND), HDR3.1 (GND), HDR3.2 (GND), HDR4.1 (GND), HDR4.2 (GND), R2.2, R4.2, R5.2, R6.1, R10.2, R12.1, S1.1 (GND), S1.5 (GND), S1.6 (GND), S1.8 (~CS), S1.12 (GND), SW2.2 (B), U2.1 (GND), U2.40 (GND), U2.41 (GND(EP)), U3.2 (GND), U5.2 (GAIN_SLOT), U5.3 (GND), U5.11 (GND), U5.15 (GND), U5.17 (EP), U6.2 (S), U7.2 (L/R), U7.3 (GND), U8.2 (GND), U9.2, USB1.1 (SHIELD), USB1.2 (SHIELD), USB1.3 (SHIELD), USB1.4 (SHIELD), USB1.A1 (GND), USB1.A12 (GND), USB1.B1 (GND), USB1.B12 (GND)
IO0: R7.2, SW2.1 (A), U2.27 (IO0)
LCD_BL: R12.2, U2.15 (IO3), U6.1 (G)
LCD_BL_FET_D: R9.1, U6.3 (D)
LCD_DC: S1.7 (DC), U2.16 (IO46)
LCD_LEDK: R9.2, S1.2 (LEDK)
LCD_RST: S1.11 (~RST), U2.19 (IO11)
LCD_SCL: S1.9 (SCL), U2.17 (IO9)
LCD_SDA: S1.10 (SDA), U2.18 (IO10)
SERVO1: HDR1.6 (SIG_B), U2.10 (IO17)
SERVO2: HDR1.5 (SIG_A), U2.11 (IO18)
SERVO3: HDR3.5 (SIG_A), U2.32 (IO39)
SERVO4: HDR3.6 (SIG_B), U2.31 (IO38)
SERVO5: HDR4.6 (SIG_B), U2.12 (IO8)
SERVO6: HDR4.5 (SIG_A), U2.20 (IO12)
USB_CC1: R5.1, USB1.A5 (CC1)
USB_CC2: R4.1, USB1.B5 (CC2)
USB_DM_32: U2.13 (IO19/USB_D-), USB1.A7 (D-), USB1.B7 (D-)
USB_DP_32: U2.14 (IO20/USB_D+), USB1.A6 (D+), USB1.B6 (D+)
VBAT: C8.1, C9.1, CN1.1, R1.1, SW1.2, SW1.5, U8.3 (BAT), U9.1
VBAT_IN: C1.1, C13.1, C14.1, HDR1.3 (V+), HDR1.4 (V+), HDR3.3 (V+), HDR3.4 (V+), HDR4.3 (V+), HDR4.4 (V+), R11.2, SW1.4, SW1.6, U3.1 (VIN), U3.3 (EN), U5.7 (VDD), U5.8 (VDD)
VCC_3V3: C2.2, C3.2, C5.2, C10.1, C11.1, R3.2, R7.1, S1.3 (LEDA), S1.4 (VDD), U2.2 (3V3), U3.5 (VOUT), U7.5 (VDD)
VO+: C15.1, CN2.1, L2.2
VO-: C12.2, CN2.2, L1.2
VUSB: C7.1, R8.1, U8.4 (VCC), USB1.A4 (VBUS), USB1.A9 (VBUS), USB1.B4 (VBUS), USB1.B9 (VBUS)

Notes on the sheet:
MCU ESP32-S3-WROOM-1U-N16R8
USB-C (nap code + sac)
Nguon: sac pin TP4054, LDO 3.3V, cong tac, do pin
Am thanh: mic I2S ICS-43434, ampli MAX98357A, loa
Man hinh LCD 1.54in 240x240 (mat sau board)
Servo (HDR1 chan trai, HDR3 chan phai, HDR4 tay / servo mo rong)

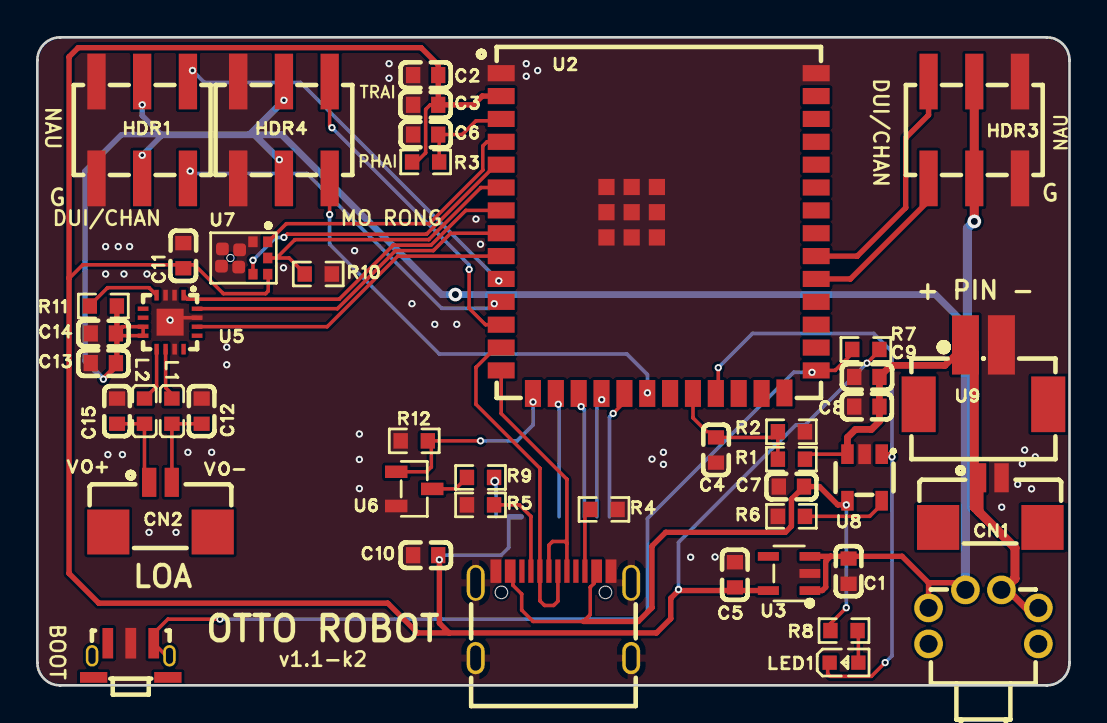
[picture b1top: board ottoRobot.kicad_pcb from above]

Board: 2 copper layers, 57.3 x 36.0 mm, 46 parts (1 on the bottom side), 39 nets.

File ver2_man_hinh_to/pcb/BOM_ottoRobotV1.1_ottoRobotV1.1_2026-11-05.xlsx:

No. | Quantity | Comment | Designator | Footprint | Value | Manufacturer Part | Manufacturer | Supplier Part | Supplier
1 | 5 | 10uF | C1,C2,C5,C8,C13 | C0603 | 10uF | CL10A106KP8NNNC | SAMSUNG(三星) | C19702 | LCSC
2 | 6 | 100nF | C3,C4,C9,C10,C11,C14 | C0603 | 100nF | CC0603KRX7R9BB104 | YAGEO(国巨) | C14663 | LCSC
3 | 1 | 1uF | C6 | C0603 | 1uF | CL10A105KB8NNNC | SAMSUNG(三星) | C15849 | LCSC
4 | 1 | 4.7uF | C7 | C0603 | 4.7uF | CL10A475KO8NNNC | SAMSUNG(三星) | C19666 | LCSC
5 | 2 | 220pF | C12,C15 | C0603 | 220pF | CL10B221KB8NNNC | SAMSUNG(三星) | C1603 | LCSC
6 | 2 | HC-1.25-2PLT | CN1,CN2 | CONN-SMD_HC-1.25-2PLT |  | HC-1.25-2PLT | HCTL(华灿天禄) | C2845388 | LCSC
7 | 3 | PZ254-2-03-S | HDR1,HDR3,HDR4 | HDR-SMD_6P-P2.54-V-M-R2-C3-LS7.5-2 |  | PZ254-2-03-S | HCTL(华灿天禄) | C3294461 | LCSC
8 | 2 | BLM18PG121SN1D | L1,L2 | L0603 |  | BLM18PG121SN1D | muRata(村田) | C14709 | LCSC
9 | 1 | KT-0603R | LED1 | LED0603-RD |  | KT-0603R | KENTO | C2286 | LCSC
10 | 2 | 100kΩ | R1,R2 | R0603 | 100kΩ | 0603WAF1003T5E | UNI-ROYAL(厚声) | C25803 | LCSC
11 | 3 | 10kΩ | R3,R7,R12 | R0603 | 10kΩ | 0603WAF1002T5E | UNI-ROYAL(厚声) | C25804 | LCSC
12 | 2 | 5.1kΩ | R4,R5 | R0603 | 5.1kΩ | 0603WAF5101T5E | UNI-ROYAL(厚声) | C23186 | LCSC
13 | 1 | 2kΩ | R6 | R0603 | 2kΩ | 0603WAF2001T5E | UNI-ROYAL(厚声) | C22975 | LCSC
14 | 1 | 1kΩ | R8 | R0603 | 1kΩ | 0603WAF1001T5E | UNI-ROYAL(厚声) | C21190 | LCSC
15 | 1 | 10Ω | R9 | R0603 | 10Ω | 0603WAF100JT5E | UNI-ROYAL(厚声) | C22859 | LCSC
16 | 2 | 1MΩ | R10,R11 | R0603 | 1MΩ | 0603WAF1004T5E | UNI-ROYAL(厚声) | C22935 | LCSC
17 | 1 | LCD-240x240 | S1 | LCD-240x240-FlUSH-154
18 | 1 | XKB5858-Z-E | SW1 | SW-TH_XKB5858-Z-E |  | XKB5858-Z-E | XKB Connection(中国星坤) | C780038 | LCSC
19 | 1 | TS35CA | SW2 | KEY-SMD_TS35CA |  | TS35CA | SHOU HAN(首韩) | C412366 | LCSC
20 | 1 | ESP32-S3-WROOM-1U-N16R8 | U2 | WIRELM-SMD_ESP32-S3-WROOM-1U |  | ESP32-S3-WROOM-1U-N16R8 | ESPRESSIF(乐鑫) | C3013946 | LCSC
21 | 1 | HE9073A33M5R | U3 | SOT-23-5_L3.0-W1.7-P0.95-LS2.8-BL |  | HE9073A33M5R | HEERMICR(赫尔半导体) | C723789 | LCSC
22 | 1 | MAX98357AETE+T | U5 | TQFN-16_L3.0-W3.0-P0.50-BL-EP1.5 |  | MAX98357AETE+T | ADI(亚德诺)/MAXIM(美信) | C910544 | LCSC
23 | 1 | AO3400A | U6 | SOT-23-3_L2.9-W1.3-P1.90-LS2.4-BR |  | AO3400A | UMW(友台半导体) | C347475 | LCSC
24 | 1 | ICS-43434 | U7 | MIC-SMD_6P-L3.5-W2.7-P0.90-BL |  | ICS-43434 | TDK InvenSense(应美盛) | C5656610 | LCSC
25 | 1 | TP4054 | U8 | TSOT-23-5_L2.9-W1.6-P0.95-LS2.8-BR |  | TP4054 | UMW(友台半导体) | C668215 | LCSC
26 | 1 | ZX-PH2.0-LT2P | U9 | CONN-SMD_2P-P2.00_ZX-PH2.0-LT2P |  | ZX-PH2.0-LT2P | Megastar(兆星) | C7429698 | LCSC
27 | 1 | typec | USB1 | USB-C-SMD_KH-TYPE-C-16P |  | typec |  | C9900016956 | LCSC
